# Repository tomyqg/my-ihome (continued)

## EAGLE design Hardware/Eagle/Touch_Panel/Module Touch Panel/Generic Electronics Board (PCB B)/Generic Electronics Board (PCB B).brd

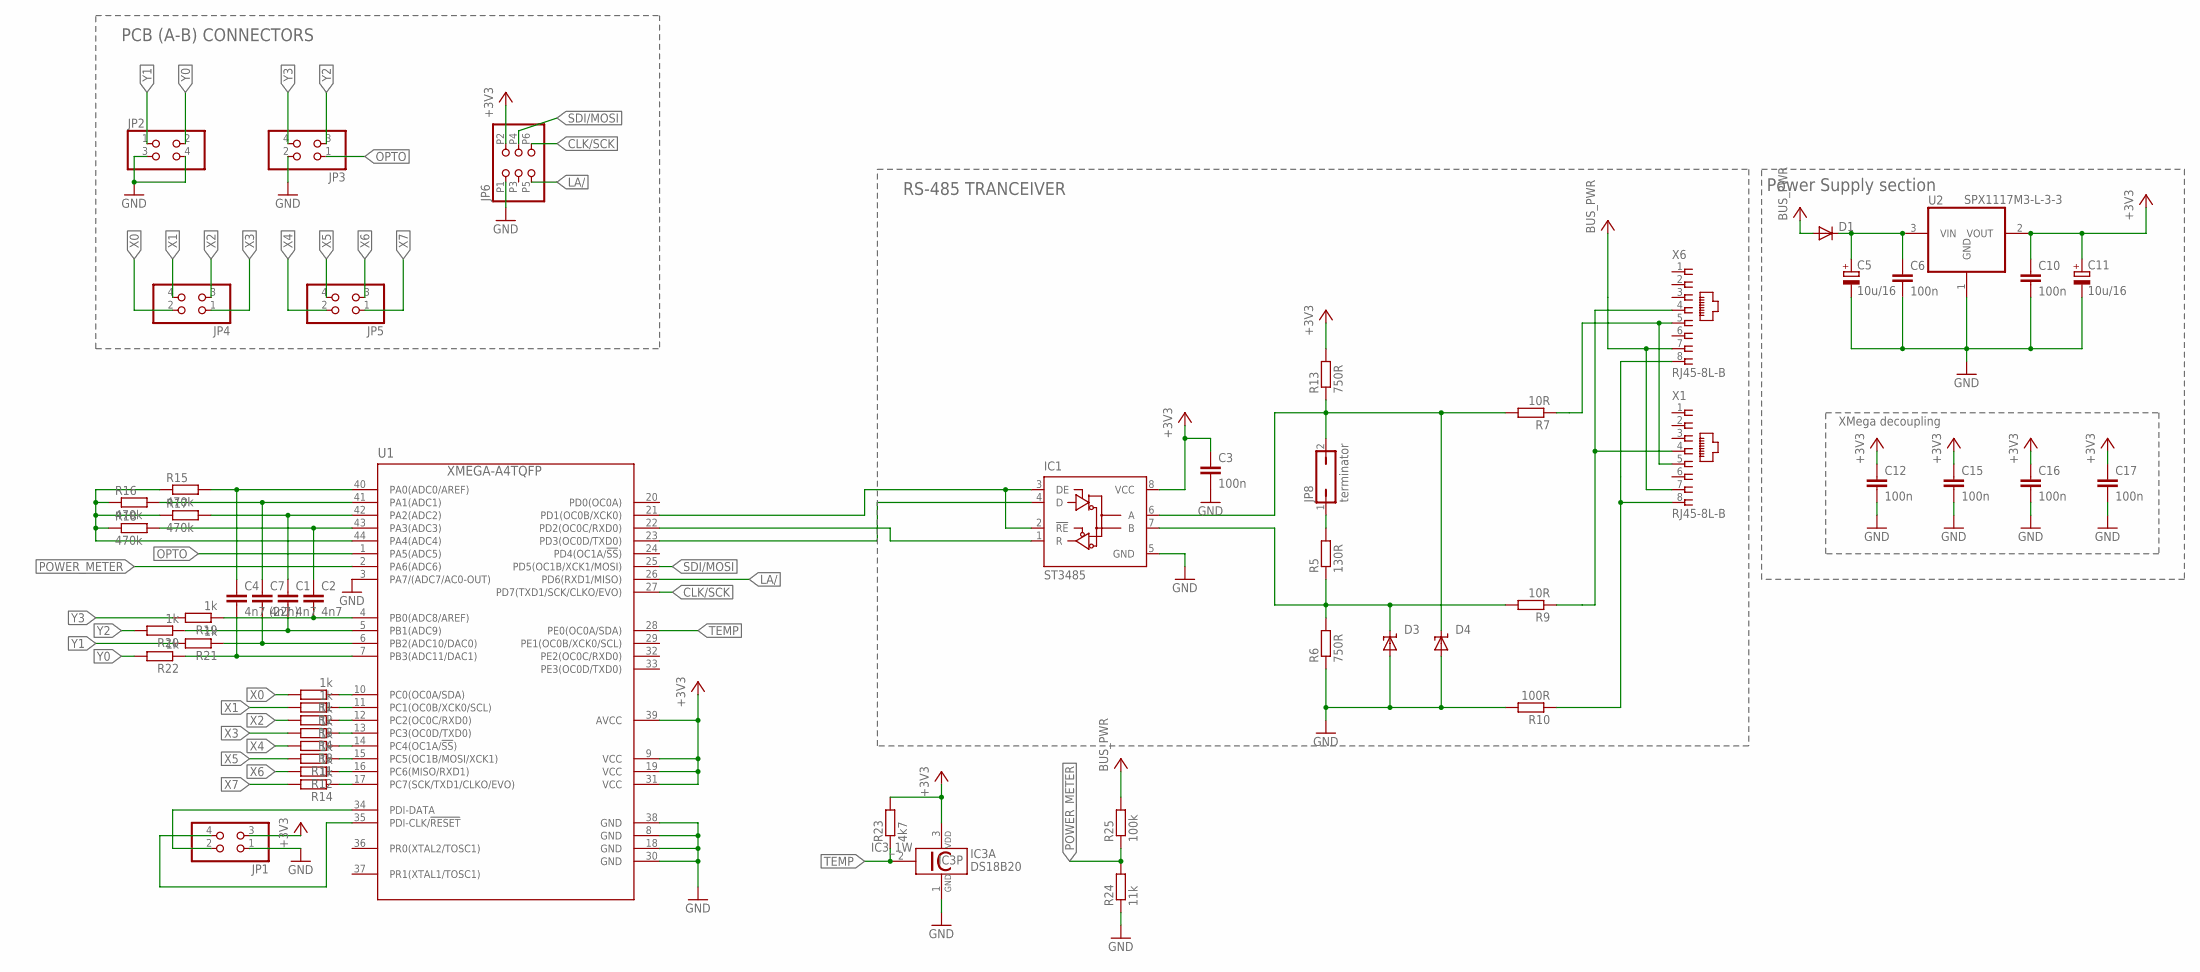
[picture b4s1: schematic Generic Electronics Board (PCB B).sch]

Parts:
C1, C2, C7: 4n7; C0603
C3, C6, C10, C12, C15, C16, C17: 100n; C0603
C4: 4n7 (22n); C0603
C5, C11: 10u/16; SMC_C
D1: DIODE-DO-214AC; DO-214AC
D3, D4: SUPPRESSOR-SMBJ; SMBJ
IC1: ST3485; D_R-PDSO-G8
IC3: DS18B20; TO92-
JP1: PINHD-2X2SMD; 2X2SMD
JP2, JP3, JP4, JP5: PINHD-2X2; 2X02
JP6: PINHD-2X3SMD; 2X3SMD
JP8: terminator; JP1
R1, R2, R3, R4, R8, R11, R12, R14, R19, R20, R21, R22: 1k; R0603
R5: 130R; R0603
R6, R13: 750R; R0603
R7, R9: 10R; R0603
R10: 100R; R0603
R15, R16, R17, R18: 470k; R0603
R23: 4k7; R0603
R24: 11k; R0603
R25: 100k; R0603
U1: XMEGA-A4TQFP; TQFP44
U2: SPX1117M3-L-3-3; SOT223
X1: RJ45-8L-B; RJ45-NO-SHIELD; MPN RJ45-8L-B
X6: RJ45-8L-B; RJ45-NO-SHIELD

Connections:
+3V3: C3.1, C10.1, C11.+, C12.1, C15.1, C16.1, C17.1, IC1.8 (VCC), IC3.3 (VDD), JP1.3, JP6.P2 (2), R13.2, R23.2, U1.9 (VCC), U1.19 (VCC), U1.31 (VCC), U1.39 (AVCC), U2.2 (VOUT)
+12V: C5.+, C6.1, D1.C, U2.3 (VIN)
BUS_PWR: D1.A, R25.2, X1.7, X6.7
CLK/SCK: JP6.P6 (6), U1.27 (PD7(TXD1/SCK/CLKO/EVO))
GND: C3.2, C5.-, C6.2, C10.2, C11.-, C12.2, C15.2, C16.2, C17.2, D3.A, D4.A, IC1.5 (GND), IC3.1 (GND), JP1.1, JP2.3, JP2.4, JP3.2, JP6.P1 (1), R6.1, R10.2, R24.1, U1.3 (PA7/(ADC7/AC0-OUT)), U1.8 (GND), U1.18 (GND), U1.30 (GND), U1.38 (GND), U2.1 (GND)
GND_RS485: R10.1, X1.8, X6.8
LA/: JP6.P5 (5), U1.26 (PD6(RXD1/MISO))
unnamed: R1.1, U1.10 (PC0(OC0A/SDA))
unnamed: R2.1, U1.11 (PC1(OC0B/XCK0/SCL))
unnamed: IC1.1 (R), U1.22 (PD2(OC0C/RXD0))
unnamed: IC1.4 (D), U1.23 (PD3(OC0D/TXD0))
unnamed: IC1.2 (!RE), IC1.3 (DE), U1.21 (PD1(OC0B/XCK0))
unnamed: R8.1, U1.14 (PC4(OC1A/!SS!))
unnamed: R11.1, U1.15 (PC5(OC1B/MOSI/XCK1))
unnamed: R12.1, U1.16 (PC6(MISO/RXD1))
unnamed: R14.1, U1.17 (PC7(SCK/TXD1/CLKO/EVO))
unnamed: D3.C, IC1.7 (B), R5.1, R6.2, R9.2
unnamed: JP8.1, R5.2
unnamed: C2.1, R18.2, U1.43 (PA3(ADC3))
unnamed: C2.2, R19.1, U1.4 (PB0(ADC8/AREF))
unnamed: C1.2, R20.1, U1.5 (PB1(ADC9))
unnamed: C1.1, R17.2, U1.42 (PA2(ADC2))
unnamed: C7.2, R21.1, U1.6 (PB2(ADC10/DAC0))
unnamed: C4.2, R22.1, U1.7 (PB3(ADC11/DAC1))
unnamed: C7.1, R16.2, U1.41 (PA1(ADC1))
unnamed: C4.1, R15.2, U1.40 (PA0(ADC0/AREF))
unnamed: R15.1, R16.1, R17.1, R18.1, U1.44 (PA4(ADC4))
OPTO: JP3.1, U1.1 (PA5(ADC5))
PC2: R3.1, U1.12 (PC2(OC0C/RXD0))
PC3: R4.1, U1.13 (PC3(OC0D/TXD0))
PDI_CLK: JP1.4, U1.35 (PDI-CLK/!RESET)
PDI_DATA: JP1.2, U1.34 (PDI-DATA)
POWER_METER: R24.2, R25.1, U1.2 (PA6(ADC6))
RS485_A: R7.1, X1.5, X6.5
RS485_A2: D4.C, IC1.6 (A), JP8.2, R7.2, R13.1
RS485_B: R9.1, X1.4, X6.4
SDI/MOSI: JP6.P4 (4), U1.25 (PD5(OC1B/XCK1/MOSI))
TEMP: IC3.2 (1W), R23.1, U1.28 (PE0(OC0A/SDA))
X0: JP4.2, R1.2
X1: JP4.4, R2.2
X2: JP4.3, R3.2
X3: JP4.1, R4.2
X4: JP5.2, R8.2
X5: JP5.4, R11.2
X6: JP5.3, R12.2
X7: JP5.1, R14.2
Y0: JP2.2, R22.2
Y1: JP2.1, R21.2
Y2: JP3.3, R20.2
Y3: JP3.4, R19.2

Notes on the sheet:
RS-485 TRANCEIVER
Power Supply section
XMega decoupling
PCB (A-B) CONNECTORS

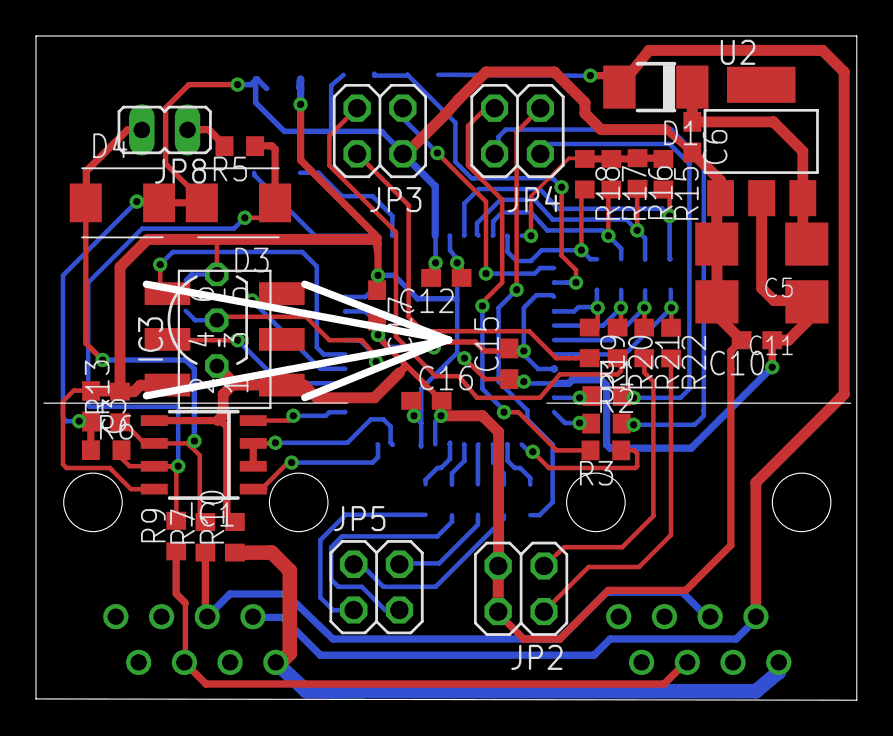
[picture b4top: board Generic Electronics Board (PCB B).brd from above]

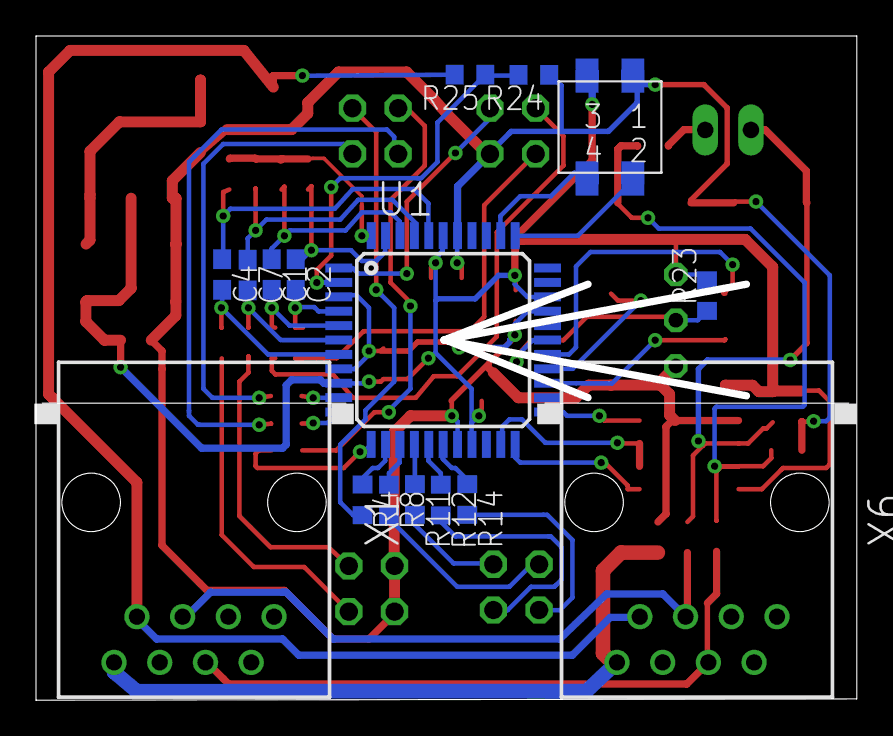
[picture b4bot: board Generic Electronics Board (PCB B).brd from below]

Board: 2 copper layers, 45.2 x 36.5 mm, 54 parts (16 on the bottom side), 50 nets.

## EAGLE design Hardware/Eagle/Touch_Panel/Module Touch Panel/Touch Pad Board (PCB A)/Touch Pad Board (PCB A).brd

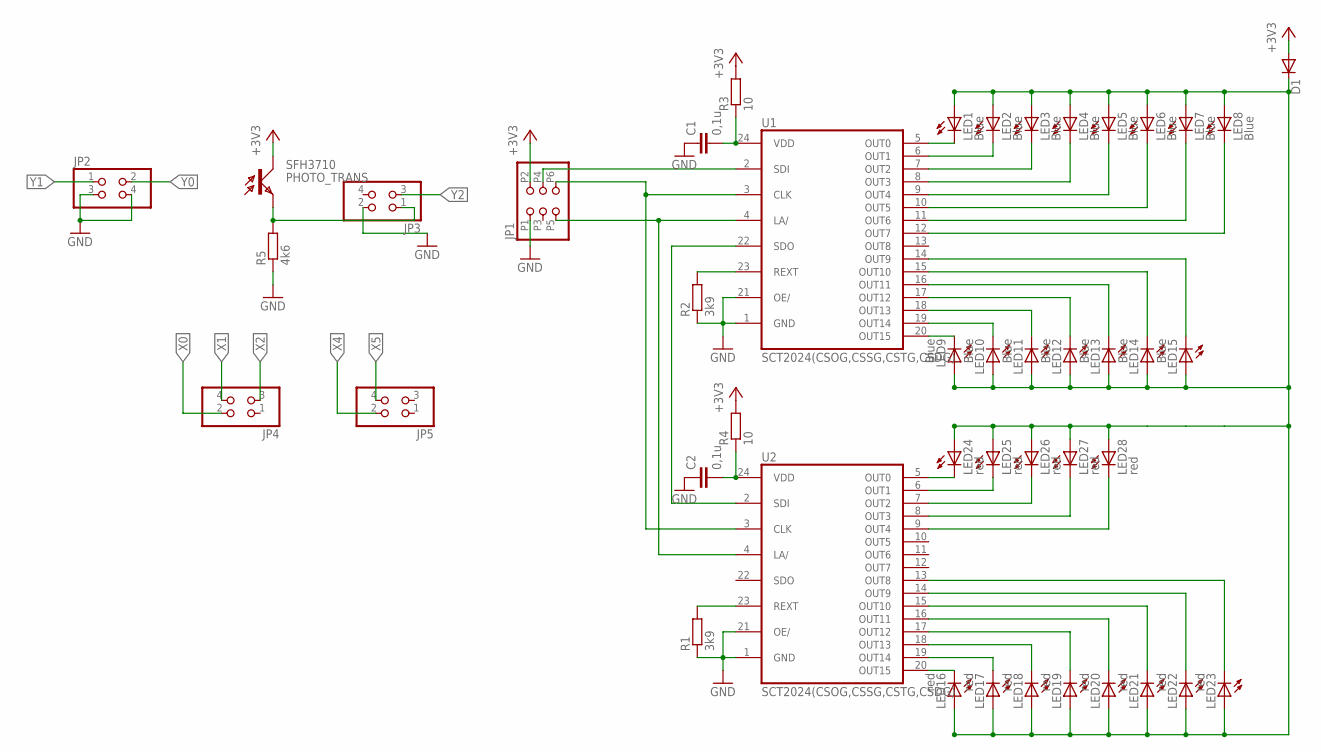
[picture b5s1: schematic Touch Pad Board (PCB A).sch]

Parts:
C1, C2: 0,1u; C0805
D1: DIODE-DO214AC; DO214AC
JP1: PINHD-2X3SMD; 2X3SMD
JP2, JP3, JP4, JP5: PINHD-2X2SMD; 2X2SMD
LED1, LED2, LED3, LED4, LED5, LED6, LED7, LED8, LED9, LED10, LED11, LED12, LED13, LED14, LED15: Blue; CHIPLED_1206
LED16, LED17, LED18, LED19, LED20, LED21, LED22, LED23, LED24, LED25, LED26, LED27, LED28: red; CHIPLED_1206
R1, R2: 3k9; R0805
R3, R4: 10; R0805
R5: 4k6; R0805
SFH3710: PHOTO_TRANS
U1, U2: SCT2024(CSOG,CSSG,CSTG,CSDG); 24SSOP

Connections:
+3V3: D1.A, JP1.P2 (2), R3.2, R4.2, SFH3710.A (C)
GND: C1.1, C2.1, JP1.P1 (1), JP2.3, JP2.4, JP3.2, R1.1, R2.1, R5.1, U1.1 (GND), U1.21 (OE/), U2.1 (GND), U2.21 (OE/)
LED_DP: D1.C, LED1.A, LED2.A, LED3.A, LED4.A, LED5.A, LED6.A, LED7.A, LED8.A, LED9.A, LED10.A, LED11.A, LED12.A, LED13.A, LED14.A, LED15.A, LED16.A, LED17.A, LED18.A, LED19.A, LED20.A, LED21.A, LED22.A, LED23.A, LED24.A, LED25.A, LED26.A, LED27.A, LED28.A
unnamed: LED1.C, U1.5 (OUT0)
unnamed: LED2.C, U1.6 (OUT1)
unnamed: LED3.C, U1.7 (OUT2)
unnamed: LED4.C, U1.8 (OUT3)
unnamed: LED5.C, U1.9 (OUT4)
unnamed: LED6.C, U1.10 (OUT5)
unnamed: LED7.C, U1.11 (OUT6)
unnamed: LED8.C, U1.12 (OUT7)
unnamed: LED24.C, U2.5 (OUT0)
unnamed: LED25.C, U2.6 (OUT1)
unnamed: LED26.C, U2.7 (OUT2)
unnamed: LED27.C, U2.8 (OUT3)
unnamed: LED28.C, U2.9 (OUT4)
unnamed: LED16.C, U2.20 (OUT15)
unnamed: LED17.C, U2.19 (OUT14)
unnamed: LED18.C, U2.18 (OUT13)
unnamed: LED19.C, U2.17 (OUT12)
unnamed: LED20.C, U2.16 (OUT11)
unnamed: LED21.C, U2.15 (OUT10)
unnamed: LED22.C, U2.14 (OUT9)
unnamed: LED23.C, U2.13 (OUT8)
unnamed: R1.2, U2.23 (REXT)
unnamed: LED9.C, U1.20 (OUT15)
unnamed: LED10.C, U1.19 (OUT14)
unnamed: LED11.C, U1.18 (OUT13)
unnamed: LED12.C, U1.17 (OUT12)
unnamed: LED13.C, U1.16 (OUT11)
unnamed: LED14.C, U1.15 (OUT10)
unnamed: LED15.C, U1.14 (OUT9)
unnamed: R2.2, U1.23 (REXT)
unnamed: U1.22 (SDO), U2.2 (SDI)
unnamed: JP1.P5 (5), U1.4 (LA/), U2.4 (LA/)
unnamed: JP1.P6 (6), U1.3 (CLK), U2.3 (CLK)
unnamed: JP1.P4 (4), U1.2 (SDI)
unnamed: C1.2, R3.1, U1.24 (VDD)
unnamed: C2.2, R4.1, U2.24 (VDD)
OPTO: JP3.1, R5.2, SFH3710.C (E)
X0: JP4.2
X1: JP4.4
X2: JP4.3
X4: JP5.2
X5: JP5.4
Y0: JP2.2
Y1: JP2.1
Y2: JP3.3

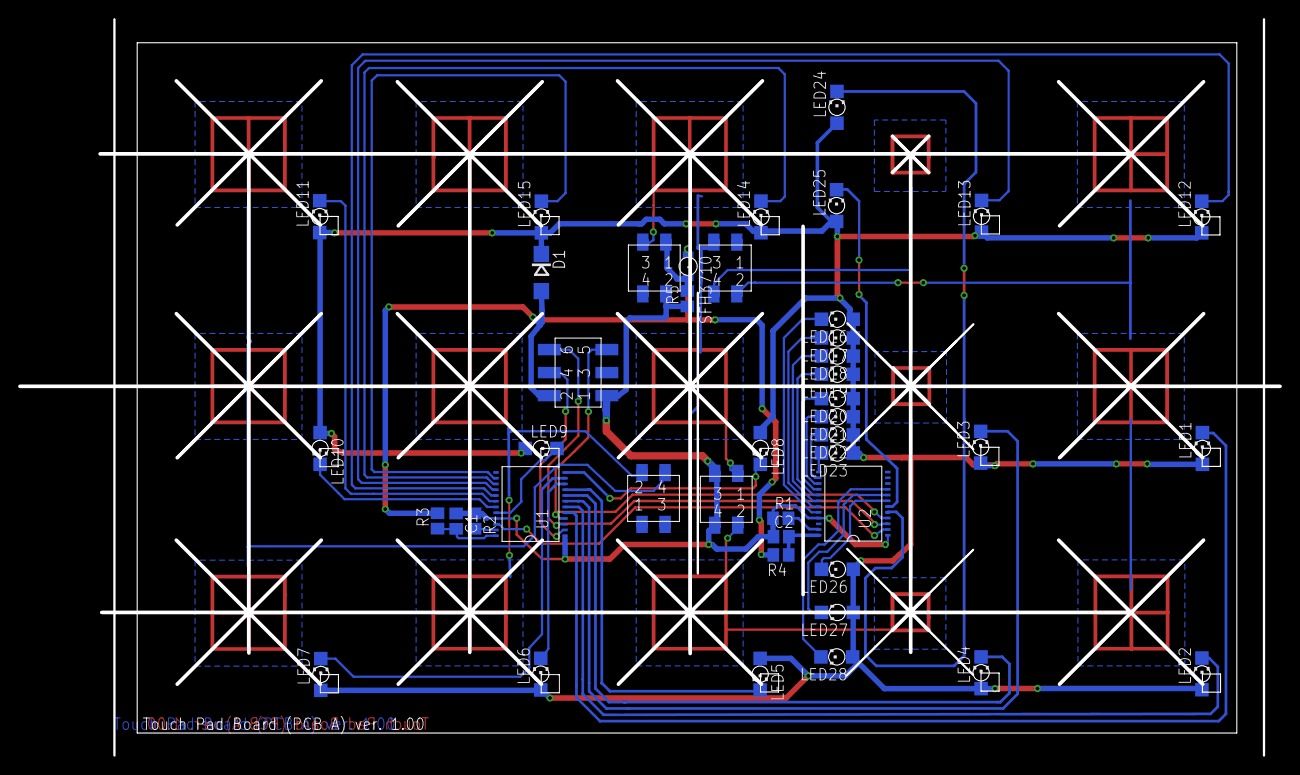
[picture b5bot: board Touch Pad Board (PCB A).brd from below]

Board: 2 copper layers, 139.1 x 81.1 mm, 44 parts (44 on the bottom side), 40 nets.

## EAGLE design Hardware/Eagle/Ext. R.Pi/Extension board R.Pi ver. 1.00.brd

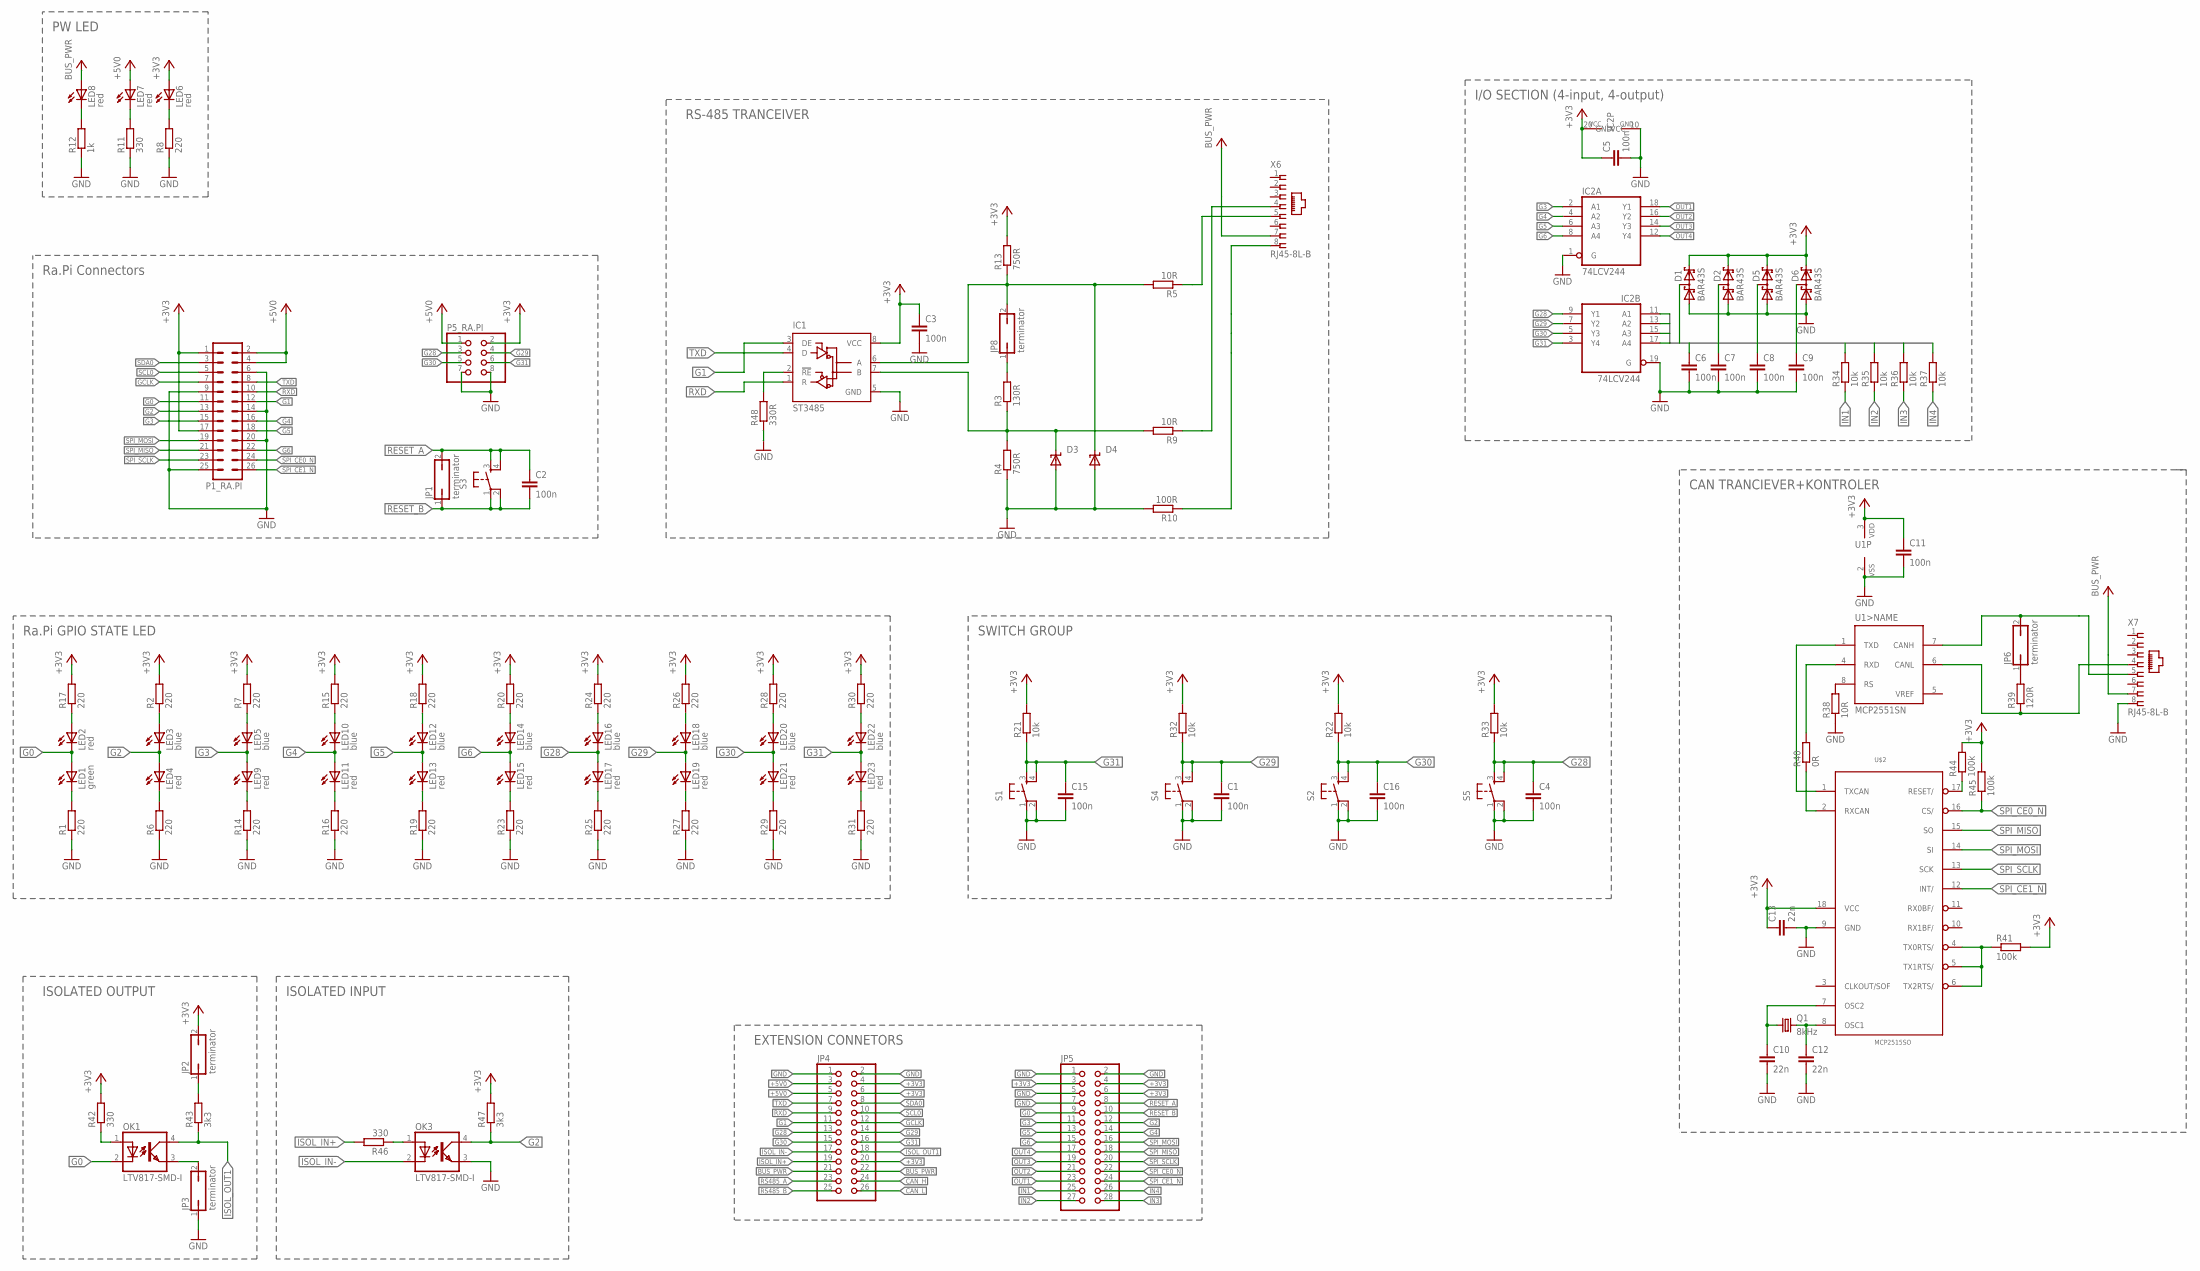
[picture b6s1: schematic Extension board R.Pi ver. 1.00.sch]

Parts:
C1, C2, C3, C4, C5, C6, C7, C8, C9, C11, C15, C16: 100n; C0805
C10, C12, C13: 22n; C0805
D1, D2, D5, D6: BAR43S; SOT23
D3, D4: SUPPRESSOR-SMBJ; SMBJ
IC1: ST3485; D_R-PDSO-G8
IC2: 74LCV244; TSSOP20
JP1, JP2, JP3, JP6, JP8: terminator; JP1
JP4: PINHD-2X13; 2X13
JP5: PINHD-2X14; 2X14
LED1: green; SML0805
LED2, LED4, LED6, LED7, LED8, LED9, LED11, LED13, LED15, LED17, LED19, LED21, LED23: red; SML0805
LED3, LED5, LED10, LED12, LED14, LED16, LED18, LED20, LED22: blue; SML0805
OK1, OK3: LTV817-SMD-I; SMD4
P1_RA.PI: MA13-2
P5_RA.PI: PINHD-2X4; 2X04
Q1: 8kHz; HC49UP
R1, R2, R6, R7, R8, R14, R15, R16, R17, R18, R19, R20, R23, R24, R25, R26, R27, R28, R29, R30, R31: 220; M0805
R3: 130R; M0805
R4, R13: 750R; M0805
R5, R9, R38: 10R; M0805
R10: 100R; M0805
R11, R42, R46: 330; M0805
R12: 1k; M0805
R21, R22, R32, R33, R34, R35, R36, R37: 10k; M0805
R39: 120R; M0805
R40: 0R; M0805
R41, R44, R45: 100k; M0805
R43, R47: 3k3; M0805
R48: 330R; M0805
S1, S2, S3, S4, S5: SPARKFUN_TAC_SWITCHSMD; SPARKFUN_TACTILE_SWITCH_SMD
U1: MCP2551SN; SO-08
U$2: MCP2515SO; SO18L
X6, X7: RJ45-8L-B; RJ45-NO-SHIELD

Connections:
+3V3: C3.1, C5.1, C11.1, C13.1, D1.2 (C2), D2.2 (C2), D5.2 (C2), D6.2 (C2), IC1.8 (VCC), IC2.20 (VCC), JP2.2, JP4.4, JP4.6, JP4.20, JP5.3, JP5.4, JP5.6, LED6.A, P1_RA.PI.1, P1_RA.PI.17, P5_RA.PI.2, R2.2, R7.2, R13.2, R15.2, R17.2, R18.2, R20.2, R21.2, R22.2, R24.2, R26.2, R28.2, R30.2, R32.2, R33.2, R41.2, R42.2, R44.2, R45.2, R47.2, U1.3 (VDD), U$2.18 (VCC)
+5V0: JP4.3, JP4.5, LED7.A, P1_RA.PI.2, P1_RA.PI.4, P5_RA.PI.1
BUS_PWR: JP4.21, JP4.22, LED8.A, X6.7, X7.7
CAN_H: JP4.24, JP6.2, U1.7 (CANH), X7.5
CAN_L: JP4.26, R39.1, U1.6 (CANL), X7.4
G0: JP5.9, LED1.A, LED2.C, OK1.2 (C), P1_RA.PI.11
G1: IC1.3 (DE), JP4.11, P1_RA.PI.12
G2: JP5.12, LED3.C, LED4.A, OK3.4 (COL), P1_RA.PI.13, R47.1
G3: IC2.2 (A1), JP5.11, LED5.C, LED9.A, P1_RA.PI.15
G4: IC2.4 (A2), JP5.14, LED10.C, LED11.A, P1_RA.PI.16
G5: IC2.6 (A3), JP5.13, LED12.C, LED13.A, P1_RA.PI.18
G6: IC2.8 (A4), JP5.15, LED14.C, LED15.A, P1_RA.PI.22
G28: C4.1, IC2.9 (Y1), JP4.13, LED16.C, LED17.A, P5_RA.PI.3, R33.1, S5.3, S5.4
G29: C1.1, IC2.7 (Y2), JP4.14, LED18.C, LED19.A, P5_RA.PI.4, R32.1, S4.3, S4.4
G30: C16.1, IC2.5 (Y3), JP4.15, LED20.C, LED21.A, P5_RA.PI.5, R22.1, S2.3, S2.4
G31: C15.1, IC2.3 (Y4), JP4.16, LED22.C, LED23.A, P5_RA.PI.6, R21.1, S1.3, S1.4
GCLK: JP4.12, P1_RA.PI.7
GND: C1.2, C3.2, C4.2, C5.2, C6.2, C7.2, C8.2, C9.2, C10.2, C11.2, C12.2, C13.2, C15.2, C16.2, D1.1 (A1), D2.1 (A1), D3.A, D4.A, D5.1 (A1), D6.1 (A1), IC1.5 (GND), IC2.1 (G), IC2.10 (GND), IC2.19 (G), JP3.1, JP4.1, JP4.2, JP5.1, JP5.2, JP5.5, JP5.7, OK3.3 (EMIT), P1_RA.PI.6, P1_RA.PI.9, P1_RA.PI.14, P1_RA.PI.20, P1_RA.PI.25, P5_RA.PI.7, P5_RA.PI.8, R1.1, R4.1, R6.1, R8.1, R10.2, R11.1, R12.1, R14.1, R16.1, R19.1, R23.1, R25.1, R27.1, R29.1, R31.1, R38.1, R48.1, S1.1, S1.2, S2.1, S2.2, S4.1, S4.2, S5.1, S5.2, U1.2 (VSS), U$2.9 (GND), X7.8
GND_RS485: R10.1, X6.8
IN1: JP5.25, R34.1
IN2: JP5.27, R35.1
IN3: JP5.28, R36.1
IN4: JP5.26, R37.1
IN_1: C6.1, D1.3 (C1A2), IC2.11 (A1), R34.2
IN_2: C7.1, D2.3 (C1A2), IC2.13 (A2), R35.2
IN_3: C8.1, D5.3 (C1A2), IC2.15 (A3), R36.2
IN_4: C9.1, D6.3 (C1A2), IC2.17 (A4), R37.2
ISOL_IN+: JP4.19, R46.2
ISOL_IN-: JP4.17, OK3.2 (C)
ISOL_OUT1: JP4.18, OK1.4 (COL), R43.1
unnamed: LED2.A, R17.1
unnamed: R38.2, U1.8 (RS)
unnamed: R40.1, U$2.2 (RXCAN)
unnamed: D3.C, IC1.7 (B), R3.1, R4.2, R9.2
unnamed: LED1.C, R1.2
unnamed: LED6.C, R8.2
unnamed: LED7.C, R11.2
unnamed: LED8.C, R12.2
unnamed: LED3.A, R2.1
unnamed: LED4.C, R6.2
unnamed: LED5.A, R7.1
unnamed: LED9.C, R14.2
unnamed: LED10.A, R15.1
unnamed: LED11.C, R16.2
unnamed: JP8.1, R3.2
unnamed: LED12.A, R18.1
unnamed: LED13.C, R19.2
unnamed: LED14.A, R20.1
unnamed: LED15.C, R23.2
unnamed: LED16.A, R24.1
unnamed: LED17.C, R25.2
unnamed: LED18.A, R26.1
unnamed: LED19.C, R27.2
unnamed: LED20.A, R28.1
unnamed: LED21.C, R29.2
unnamed: LED22.A, R30.1
unnamed: LED23.C, R31.2
unnamed: R40.2, U1.4 (RXD)
unnamed: U1.1 (TXD), U$2.1 (TXCAN)
unnamed: JP6.1, R39.2
unnamed: C12.1, Q1.2, U$2.8 (OSC1)
unnamed: C10.1, Q1.1, U$2.7 (OSC2)
unnamed: JP3.2, OK1.3 (EMIT)
unnamed: OK1.1 (A), R42.1
unnamed: OK3.1 (A), R46.1
unnamed: JP2.1, R43.2
unnamed: R41.1, U$2.4 (TX0RTS/), U$2.5 (TX1RTS/), U$2.6 (TX2RTS/)
unnamed: R44.1, U$2.17 (RESET/)
unnamed: IC1.2 (!RE), R48.2
OUT1: IC2.18 (Y1), JP5.23
OUT2: IC2.16 (Y2), JP5.21
OUT3: IC2.14 (Y3), JP5.19
OUT4: IC2.12 (Y4), JP5.17
RESET_A: C2.1, JP1.2, JP5.8, S3.3, S3.4
RESET_B: C2.2, JP1.1, JP5.10, S3.1, S3.2
RS485_A: JP4.23, R5.1, X6.5
RS485_A2: D4.C, IC1.6 (A), JP8.2, R5.2, R13.1
RS485_B: JP4.25, R9.1, X6.4
RXD: IC1.1 (R), JP4.9, P1_RA.PI.10
SCL0: JP4.10, P1_RA.PI.5
SDA0: JP4.8, P1_RA.PI.3
SPI_CE0_N: JP5.22, P1_RA.PI.24, R45.1, U$2.16 (CS/)
SPI_CE1_N: JP5.24, P1_RA.PI.26, U$2.12 (INT/)
SPI_MISO: JP5.18, P1_RA.PI.21, U$2.15 (SO)
SPI_MOSI: JP5.16, P1_RA.PI.19, U$2.14 (SI)
SPI_SCLK: JP5.20, P1_RA.PI.23, U$2.13 (SCK)
TXD: IC1.4 (D), JP4.7, P1_RA.PI.8
VREF: U1.5 (VREF)

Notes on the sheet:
Ra.Pi Connectors
RS-485 TRANCEIVER
PW LED
Ra.Pi GPIO STATE LED
SWITCH GROUP
I/O SECTION (4-input, 4-output)
ISOLATED OUTPUT
ISOLATED INPUT
EXTENSION CONNETORS
CAN TRANCIEVER+KONTROLER

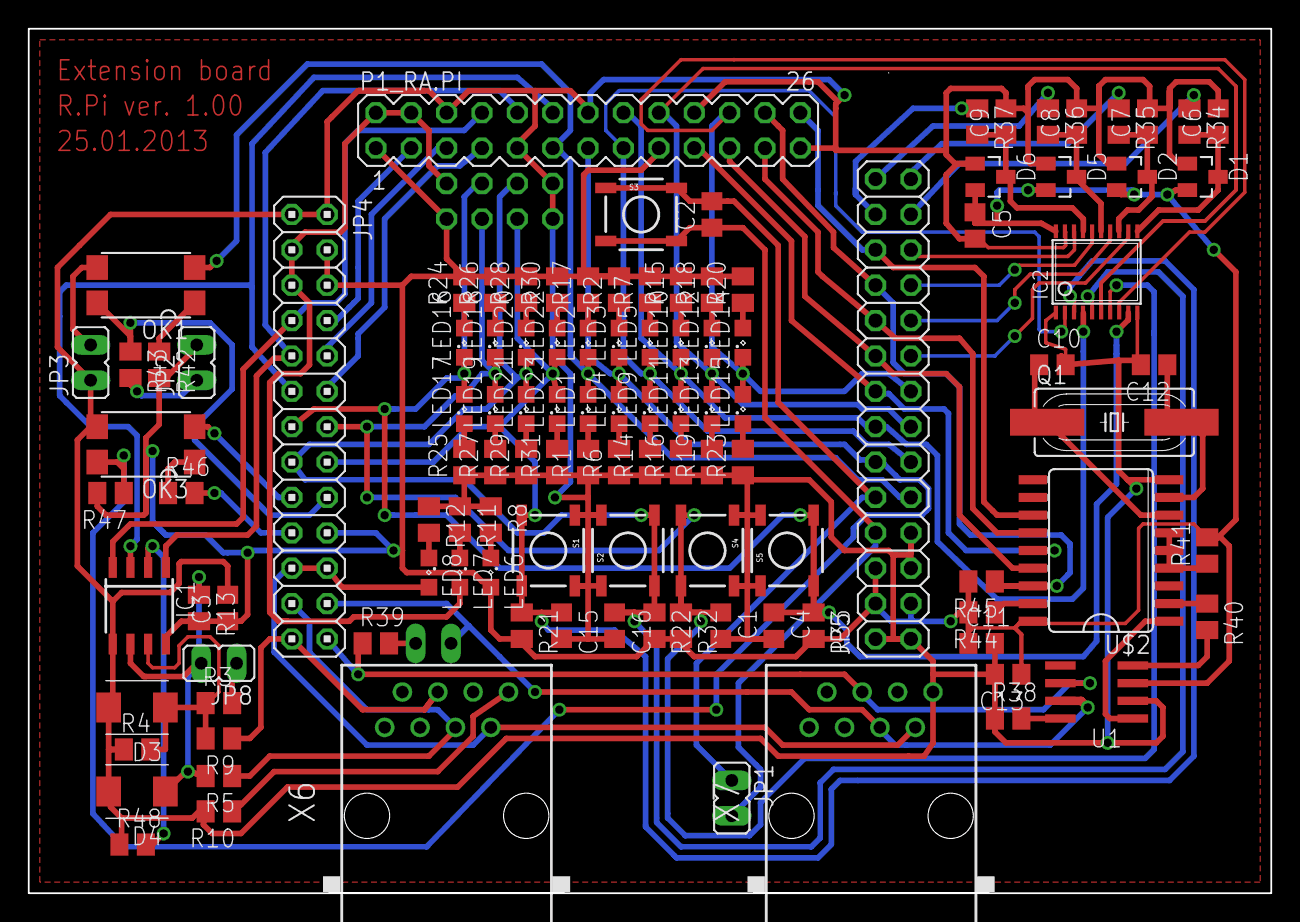
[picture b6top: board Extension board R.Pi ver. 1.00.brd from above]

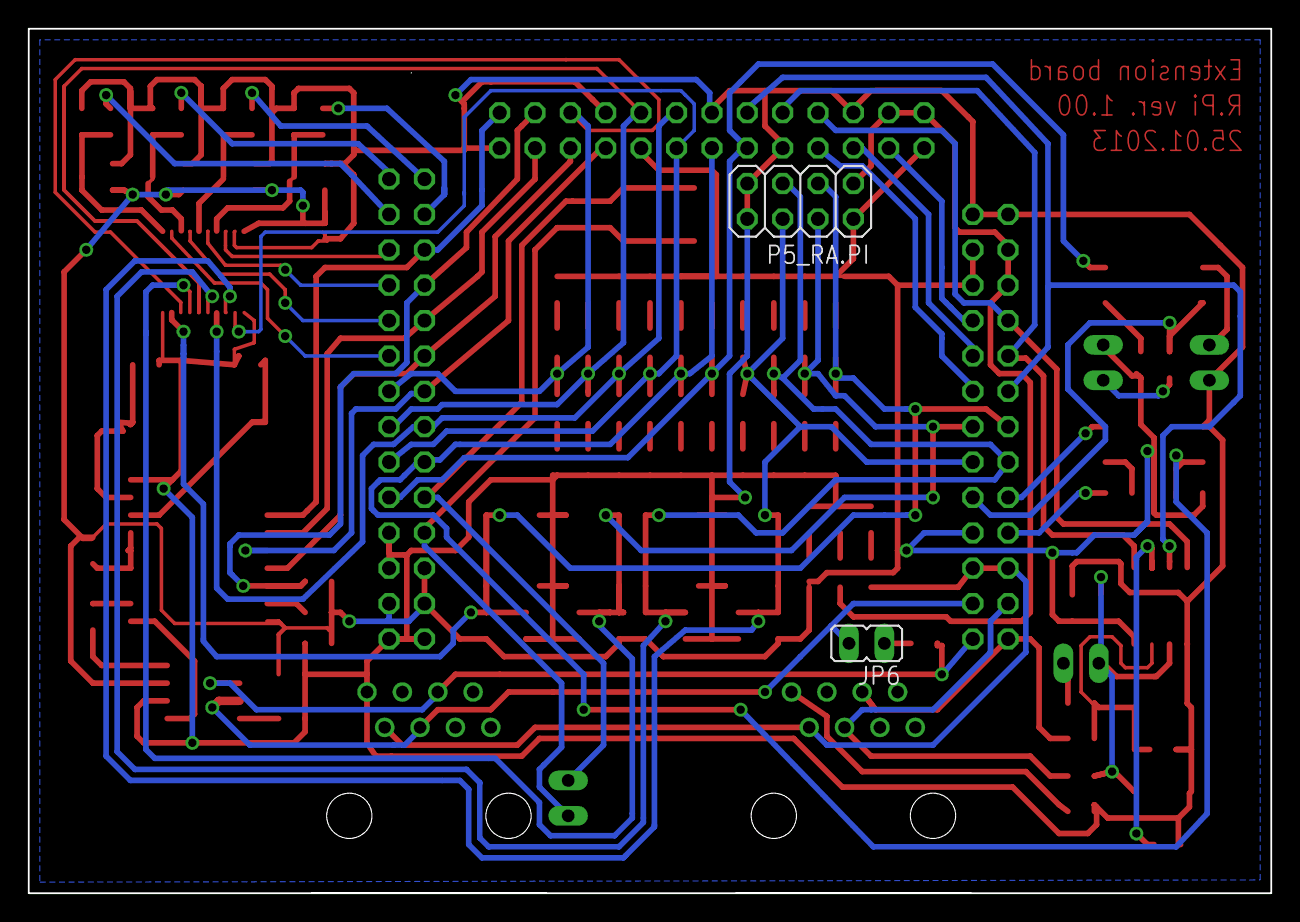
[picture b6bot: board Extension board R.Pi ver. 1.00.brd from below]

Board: 2 copper layers, 89.2 x 62.1 mm, 115 parts (2 on the bottom side), 87 nets.

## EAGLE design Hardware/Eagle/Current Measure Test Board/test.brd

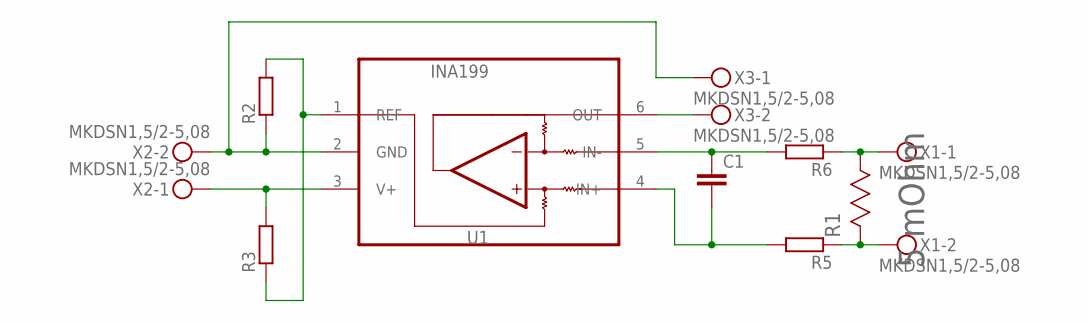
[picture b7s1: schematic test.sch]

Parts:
C1: C-EUC0805; C0805
R1: 5 mOhm; RESC6332X110N
R2, R3, R5, R6: R-EU_R0805; R0805
U1: INA199; SC70-6L
X1, X2, X3: MKDSN1,5/2-5,08

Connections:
GND: R2.1, U1.2 (GND), X2.2, X3.1
unnamed: C1.1, R6.2, U1.5 (IN-)
unnamed: C1.2, R5.2, U1.4 (IN+)
unnamed: R2.2, R3.1, U1.1 (REF)
unnamed: R1.1 (R1), R6.1, X1.1
unnamed: R1.2 (R2), R5.1, X1.2
unnamed: U1.6 (OUT), X3.2
VCC: R3.2, U1.3 (V+), X2.1

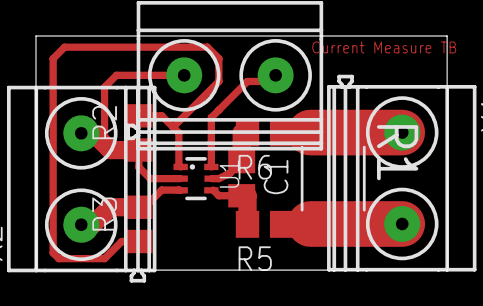
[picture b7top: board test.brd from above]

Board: 2 copper layers, 22.8 x 13.0 mm, 10 parts (0 on the bottom side), 8 nets.

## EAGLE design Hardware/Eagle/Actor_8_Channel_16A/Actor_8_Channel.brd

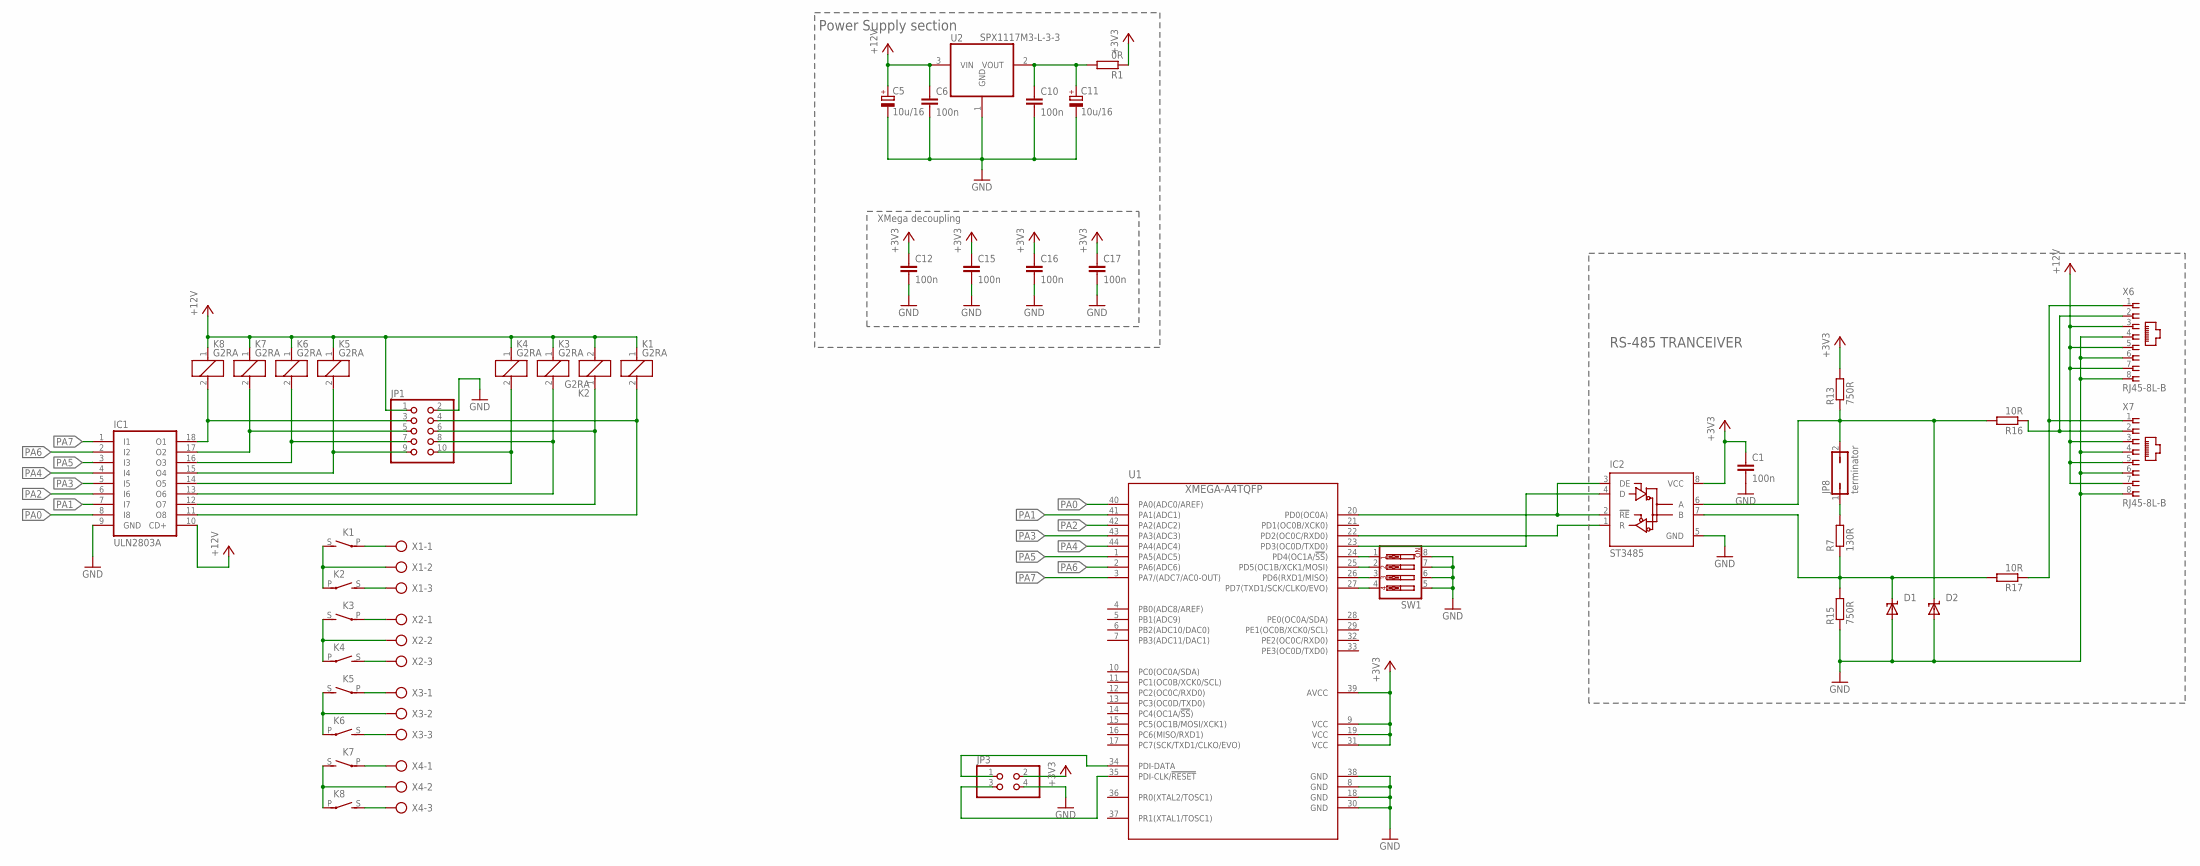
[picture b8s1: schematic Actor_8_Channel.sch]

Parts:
C1, C6, C10, C12, C15, C16, C17: 100n; C1206
C5, C11: 10u/16; SMC_C
D1, D2: SUPPRESSOR-SMBJ; SMBJ
IC1: ULN2803A; SO18W
IC2: ST3485; D_R-PDSO-G8
JP1: PINHD-2X5; 2X05
JP3: PINHD-2X2; 2X02
JP8: terminator; JP1
K1, K2, K3, K4, K5, K6, K7, K8: G2RA
R1: 0R; M1206
R7: 130R; M1206
R13, R15: 750R; M1206
R16, R17: 10R; M1206
SW1: SW_DIP-4; EDG-04
U1: XMEGA-A4TQFP; TQFP44
U2: SPX1117M3-L-3-3; SOT223
X1, X2, X3, X4: MKDS_5/3-7,5; MKDS_5/-750
X6, X7: RJ45-8L-B; RJ45-NO-SHIELD

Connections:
+3V3: C1.1, C10.1, C11.+, C12.1, C15.1, C16.1, C17.1, IC2.8 (VCC), JP3.2, R1.1, R1.2, R13.2, U1.9 (VCC), U1.19 (VCC), U1.31 (VCC), U1.39 (AVCC), U2.2 (VOUT)
+12V: C5.+, C6.1, IC1.10 (CD+), JP1.1, K1.1, K2.2, K3.1, K4.1, K5.1, K6.1, K7.1, K8.1, U2.3 (VIN), X6.3, X6.5, X6.7, X7.3, X7.5, X7.7
GND: C1.2, C5.-, C6.2, C10.2, C11.-, C12.2, C15.2, C16.2, C17.2, D1.A, D2.A, IC1.9 (GND), IC2.5 (GND), JP1.2, JP3.4, R15.1, SW1.5, SW1.6, SW1.7, SW1.8, U1.8 (GND), U1.18 (GND), U1.30 (GND), U1.38 (GND), U2.1 (GND), X6.4, X6.6, X6.8, X7.4, X7.6, X7.8
unnamed: K1.P, X1.1
unnamed: K3.P, X2.1
unnamed: K5.P, X3.1
unnamed: K7.P, X4.1
unnamed: K6.S, X3.3
unnamed: IC1.18 (O1), JP1.3, K8.2
unnamed: IC1.17 (O2), JP1.5, K7.2
unnamed: IC1.16 (O3), JP1.7, K6.2
unnamed: IC1.15 (O4), JP1.9, K5.2
unnamed: IC1.14 (O5), JP1.10, K4.2
unnamed: IC1.13 (O6), JP1.8, K3.2
unnamed: IC1.12 (O7), JP1.6, K2.1
unnamed: IC1.11 (O8), JP1.4, K1.2
unnamed: R17.1, X6.1, X7.1
unnamed: JP8.1, R7.2
unnamed: D1.C, IC2.7 (B), R7.1, R15.2, R17.2
unnamed: R16.1, X6.2, X7.2
unnamed: SW1.1, U1.24 (PD4(OC1A/!SS!))
unnamed: SW1.2, U1.25 (PD5(OC1B/XCK1/MOSI))
unnamed: SW1.3, U1.26 (PD6(RXD1/MISO))
unnamed: SW1.4, U1.27 (PD7(TXD1/SCK/CLKO/EVO))
unnamed: K1.S, K2.P, X1.2
unnamed: K2.S, X1.3
unnamed: K3.S, K4.P, X2.2
unnamed: K4.S, X2.3
unnamed: K5.S, K6.P, X3.2
unnamed: JP3.1, U1.34 (PDI-DATA)
unnamed: JP3.3, U1.35 (PDI-CLK/!RESET)
unnamed: K7.S, K8.P, X4.2
unnamed: K8.S, X4.3
PA0: IC1.8 (I8), U1.40 (PA0(ADC0/AREF))
PA1: IC1.7 (I7), U1.41 (PA1(ADC1))
PA2: IC1.6 (I6), U1.42 (PA2(ADC2))
PA3: IC1.5 (I5), U1.43 (PA3(ADC3))
PA4: IC1.4 (I4), U1.44 (PA4(ADC4))
PA5: IC1.3 (I3), U1.1 (PA5(ADC5))
PA6: IC1.2 (I2), U1.2 (PA6(ADC6))
PA7: IC1.1 (I1), U1.3 (PA7/(ADC7/AC0-OUT))
PD_0: IC2.2 (!RE), IC2.3 (DE), U1.20 (PD0(OC0A))
PD_2: IC2.1 (R), U1.22 (PD2(OC0C/RXD0))
PD_3: IC2.4 (D), U1.23 (PD3(OC0D/TXD0))
RS485_A1: D2.C, IC2.6 (A), JP8.2, R13.1, R16.2

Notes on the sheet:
Power Supply section
XMega decoupling
RS-485 TRANCEIVER
